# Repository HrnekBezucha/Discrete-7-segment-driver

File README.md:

# Discrete-7-segment-driver
7-segment display driver with a discrete diode ROM

The matrix of diodes is hardwired memory.
Each row is one word/byte with the 
length of 7 bits. The circuit 'stores' data
for displaying a number on a 7 segment LED display
(hence 7 bit word)
I made the memory and the display from
discrete diodes and the only chips are for
changing the address. Counting up at 1Hz frequency.
It would also work by putting logic HIGH on anode
of one of the leftmost diodes and get your output
on the bottom. That's where the display is wired.

It's an educational board with a bit of computer
history. This is what the pioneers of computing
used for microcode. Storing vital data, such as
the instruction set and boot sequence.

You can read some more about it on my blog
https://unregulatedpowersupply.wordpress.com/

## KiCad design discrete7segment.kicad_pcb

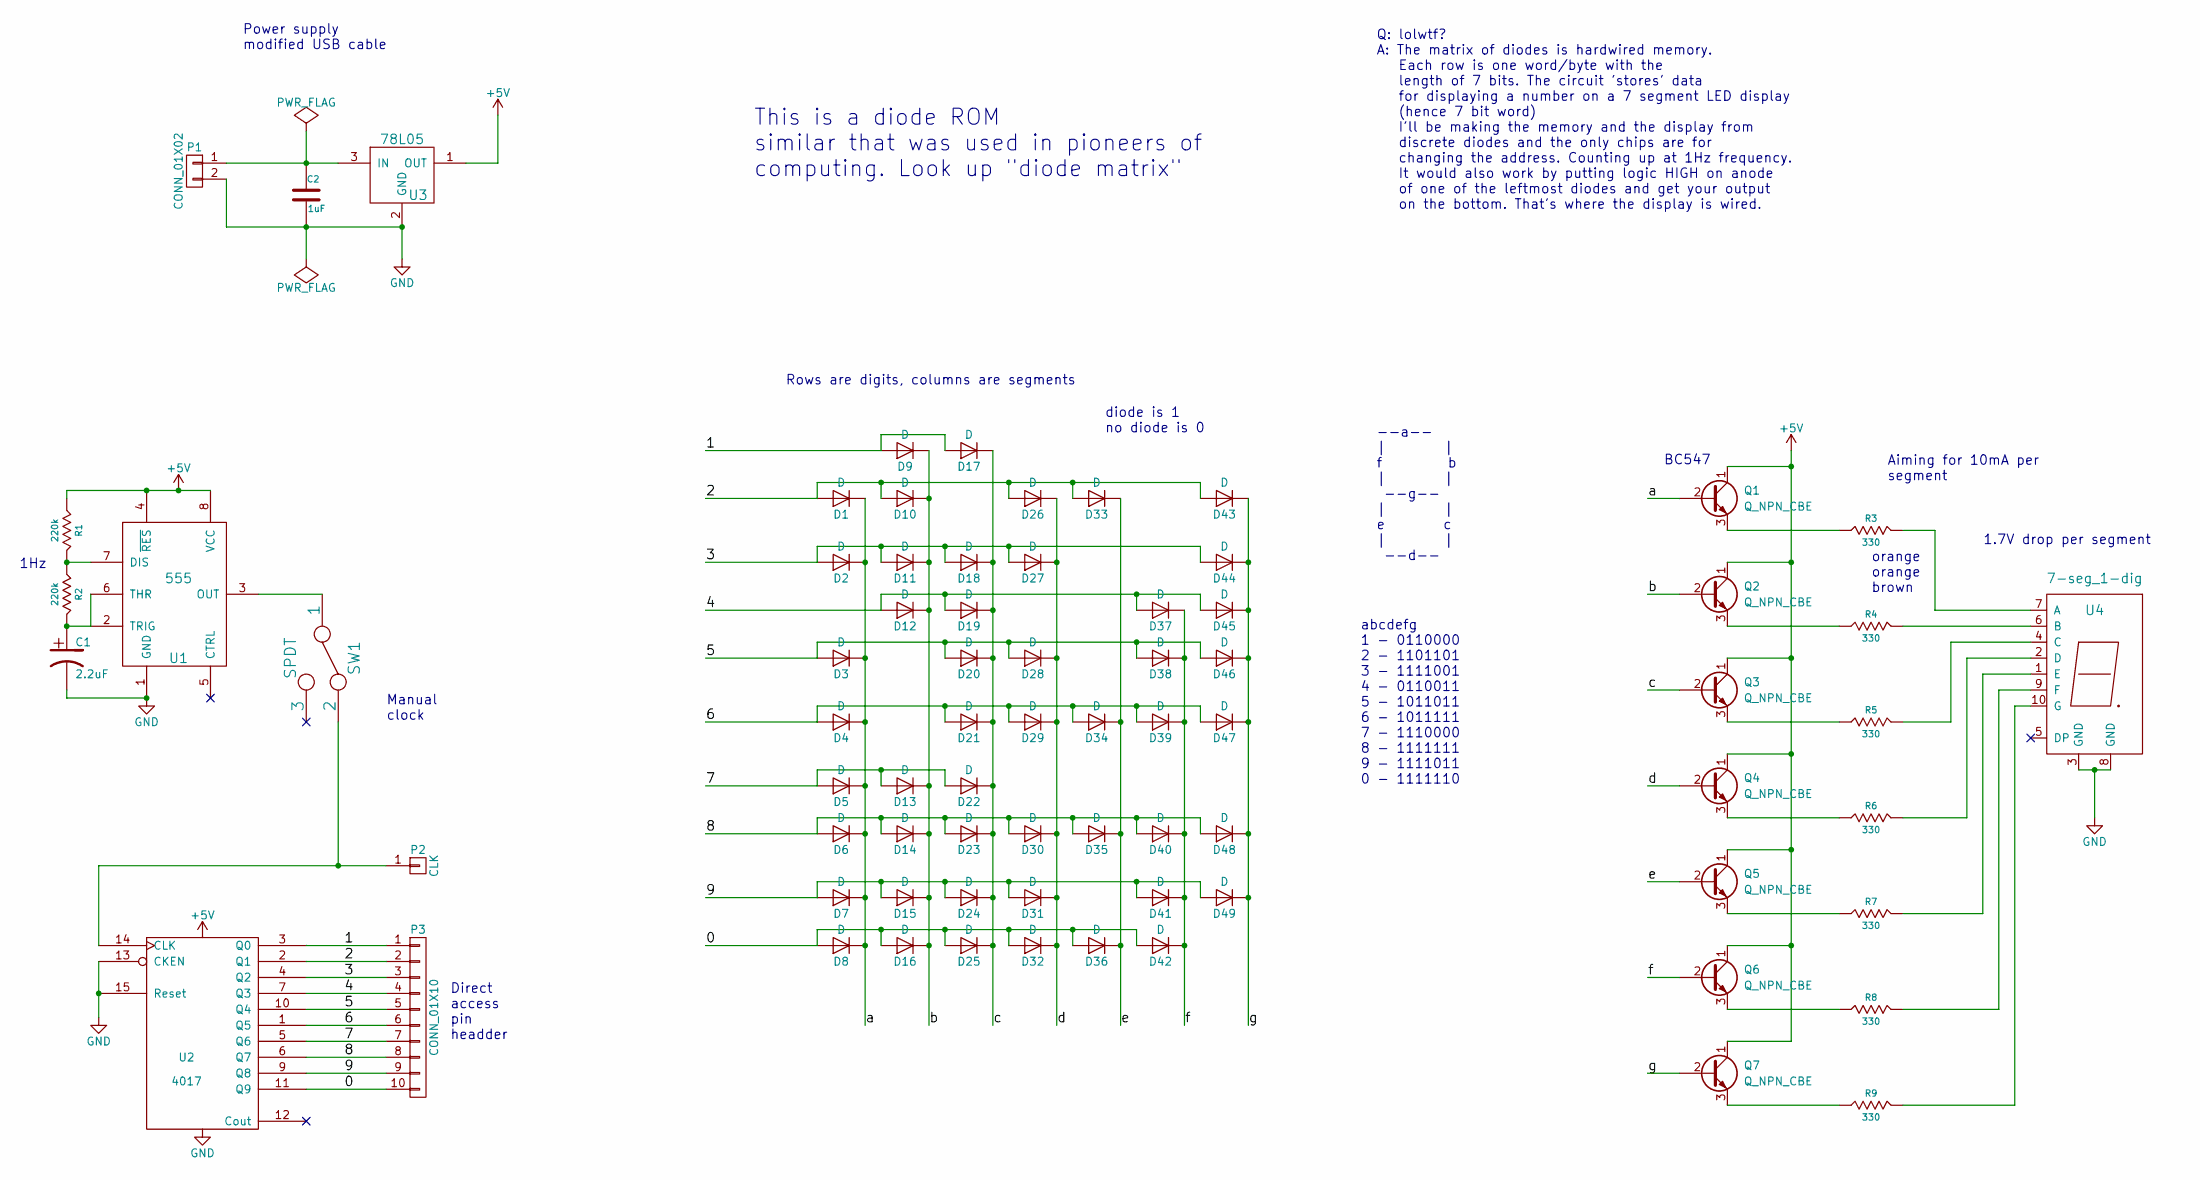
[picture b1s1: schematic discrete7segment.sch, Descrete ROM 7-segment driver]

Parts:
C1: 2.2uF; C_Radial_D5_L6_P2.5
C2: 1uF; C_Radial_D5_L6_P2.5
D1, D2, D3, D4, D5, D6, D7, D8, D9, D10, D11, D12, D13, D14, D15, D16, D17, D18, D19, D20, D21, D22, D23, D24, D25, D26, D27, D28, D29, D30, D31, D32, D33, D34, D35, D36, D37, D38, D39, D40, D41, D42, D43, D44, D45, D46, D47, D48, D49: D; Diode_DO-41_SOD81_Vertical_KathodeUp
P1: CONN_01X02; Pin_Header_Straight_1x02
P2: CLK; Pin_Header_Straight_1x01
P3: CONN_01X10; Pin_Header_Straight_1x10
Q1, Q2, Q3, Q4, Q5, Q6, Q7: Q_NPN_CBE; TO-92_Inline_Narrow_Oval
R1, R2: 220k; Resistor_Horizontal_RM7mm
R3, R4, R5, R6, R7, R8, R9: 330; Resistor_Horizontal_RM7mm
SW1: SPDT; SW_Micro_SPST
U1: 555; DIP-8_W7.62mm_LongPads
U2: 4017; DIP-16_W7.62mm_LongPads
U3: 78L05; TO-92_Inline_Narrow_Oval
U4: 7-seg_1-dig; 7SegmentLED_LTS6760_LTS6780

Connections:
+5V: Q1.1 (C), Q2.1 (C), Q3.1 (C), Q4.1 (C), Q5.1 (C), Q6.1 (C), Q7.1 (C), R1.1 (A), U1.4 (~RES), U1.8 (VCC), U2.16 (VDD), U3.1 (OUT)
/0: D8.2 (A), D16.2 (A), D25.2 (A), D32.2 (A), D36.2 (A), D42.2 (A), P3.10, U2.11 (Q9)
/1: D9.2 (A), D17.2 (A), P3.1, U2.3 (Q0)
/2: D1.2 (A), D10.2 (A), D26.2 (A), D33.2 (A), D43.2 (A), P3.2, U2.2 (Q1)
/3: D2.2 (A), D11.2 (A), D18.2 (A), D27.2 (A), D44.2 (A), P3.3, U2.4 (Q2)
/4: D12.2 (A), D19.2 (A), D37.2 (A), D45.2 (A), P3.4, U2.7 (Q3)
/5: D3.2 (A), D20.2 (A), D28.2 (A), D38.2 (A), D46.2 (A), P3.5, U2.10 (Q4)
/6: D4.2 (A), D21.2 (A), D29.2 (A), D34.2 (A), D39.2 (A), D47.2 (A), P3.6, U2.1 (Q5)
/7: D5.2 (A), D13.2 (A), D22.2 (A), P3.7, U2.5 (Q6)
/8: D6.2 (A), D14.2 (A), D23.2 (A), D30.2 (A), D35.2 (A), D40.2 (A), D48.2 (A), P3.8, U2.6 (Q7)
/9: D7.2 (A), D15.2 (A), D24.2 (A), D31.2 (A), D41.2 (A), D49.2 (A), P3.9, U2.9 (Q8)
/a: D1.1 (K), D2.1 (K), D3.1 (K), D4.1 (K), D5.1 (K), D6.1 (K), D7.1 (K), D8.1 (K), Q1.2 (B)
/b: D9.1 (K), D10.1 (K), D11.1 (K), D12.1 (K), D13.1 (K), D14.1 (K), D15.1 (K), D16.1 (K), Q2.2 (B)
/c: D17.1 (K), D18.1 (K), D19.1 (K), D20.1 (K), D21.1 (K), D22.1 (K), D23.1 (K), D24.1 (K), D25.1 (K), Q3.2 (B)
/d: D26.1 (K), D27.1 (K), D28.1 (K), D29.1 (K), D30.1 (K), D31.1 (K), D32.1 (K), Q4.2 (B)
/e: D33.1 (K), D34.1 (K), D35.1 (K), D36.1 (K), Q5.2 (B)
/f: D37.1 (K), D38.1 (K), D39.1 (K), D40.1 (K), D41.1 (K), D42.1 (K), Q6.2 (B)
/g: D43.1 (K), D44.1 (K), D45.1 (K), D46.1 (K), D47.1 (K), D48.1 (K), D49.1 (K), Q7.2 (B)
GND: C1.2, C2.2, P1.2, U1.1 (GND), U2.8 (VSS), U2.13 (CKEN), U2.15 (Reset), U3.2 (GND), U4.3 (GND), U4.8 (GND)
unnamed: C1.1, R2.2 (K), U1.2 (TRIG), U1.6 (THR)
unnamed: C2.1, P1.1, U3.3 (IN)
unnamed: P2.1, SW1.2, U2.14 (CLK)
unnamed: Q1.3 (E), R3.1 (A)
unnamed: Q2.3 (E), R4.1 (A)
unnamed: Q3.3 (E), R5.1 (A)
unnamed: Q4.3 (E), R6.1 (A)
unnamed: Q5.3 (E), R7.1 (A)
unnamed: Q6.3 (E), R8.1 (A)
unnamed: Q7.3 (E), R9.1 (A)
unnamed: R1.2 (K), R2.1 (A), U1.7 (DIS)
unnamed: R3.2 (K), U4.7 (A)
unnamed: R4.2 (K), U4.6 (B)
unnamed: R5.2 (K), U4.4 (C)
unnamed: R6.2 (K), U4.2 (D)
unnamed: R7.2 (K), U4.1 (E)
unnamed: R8.2 (K), U4.9 (F)
unnamed: R9.2 (K), U4.10 (G)
unnamed: SW1.1, U1.3 (OUT)

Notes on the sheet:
This is a diode ROM similar that was used in pioneers of computing. Look up "diode matrix"
Rows are digits, columns are segments
--a-- | | f b | | --g-- | | e c | | --d--
Power supply modified USB cable
1Hz
abcdefg 1 - 0110000 2 - 1101101 3 - 1111001 4 - 0110011 5 - 1011011 6 - 1011111 7 - 1110000 8 - 1111111 9 - 1111011 0 - 1111110
Q: lolwtf? A: The matrix of diodes is hardwired memory. Each row is one word/byte with the length of 7 bits. The circuit 'stores' data for displaying a number on a 7 segment LED display (hence 7 bit word) I'll be making the memory and the display from discrete diodes and the only chips are for chan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
diode is 1 no diode is 0
1.7V drop per segment
orange orange brown
Aiming for 10mA per segment
Manual clock
Direct access pin headder
BC547

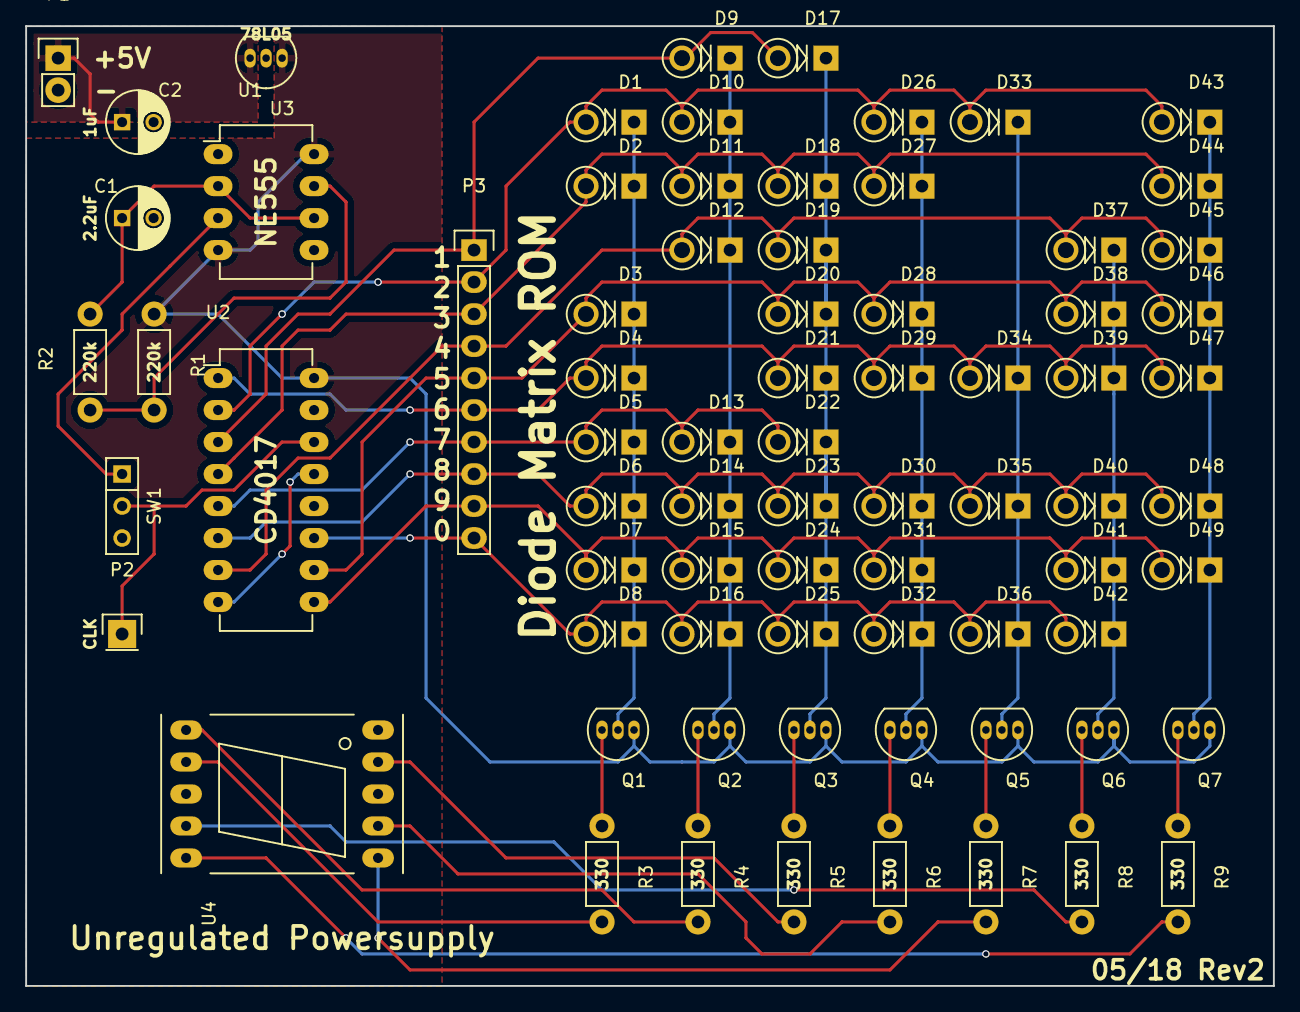
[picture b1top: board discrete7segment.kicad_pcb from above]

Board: 2 copper layers, 99.1 x 76.2 mm, 75 parts (0 on the bottom side), 38 nets.

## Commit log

2018-04-22 init
2018-04-22 formatting
2018-04-22 layout begun
2018-04-22 generated schematic pdf
2018-04-22 done digit
2018-04-22 board finished
2018-04-23 found bugs, needs rework
2018-04-25 bugfixes
2018-04-25 layout from scratch
2018-04-25 layout finished
2018-04-25 re-rendered
2018-04-25 re-re-rendered
2018-04-27 updated info
2018-05-10 bugfix
2018-05-10 details
2018-05-12 vast redesign
2018-05-12 through hole design
2018-05-12 new layout initiated
2018-05-12 layout done
2018-05-12 through hole layout
2018-05-12 THT version
2018-05-13 erc passed
2018-05-13 THT generation
